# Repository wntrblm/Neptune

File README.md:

# Winterbloom Neptune

Neptune is a *salty* diode ladder filter.

More details available at https://winterbloom.com/shop/neptune

## Repository layout

This repository contains the hardware design files and user guide for Neptune:

- **factory/** contains the scripts used to program, test, and calibrate the module after assembly. These scripts are all written in Python.
- **hardware/** contains the hardware design files for the mainboard and blank panel, as well as hardware for automated testing. These are all created using KiCAD.
- **user_guide/** contains the user's guide source files. These are written in Markdown and published using MkDocs.
- **simulation/** contains the simulation used to design this filter. These should be opened using the Falstad CircuitJS simulator https://www.falstad.com/circuit/circuitjs.html.

## License and contributing

Neptune is open-source hardware and software, however, licensing a project like this is a little complicated. Please take a chance to review the [LICENSE](LICENSE.md) file.

We welcome contributions! Please read our [Code of Conduct](CODE_OF_CONDUCT.md) first.

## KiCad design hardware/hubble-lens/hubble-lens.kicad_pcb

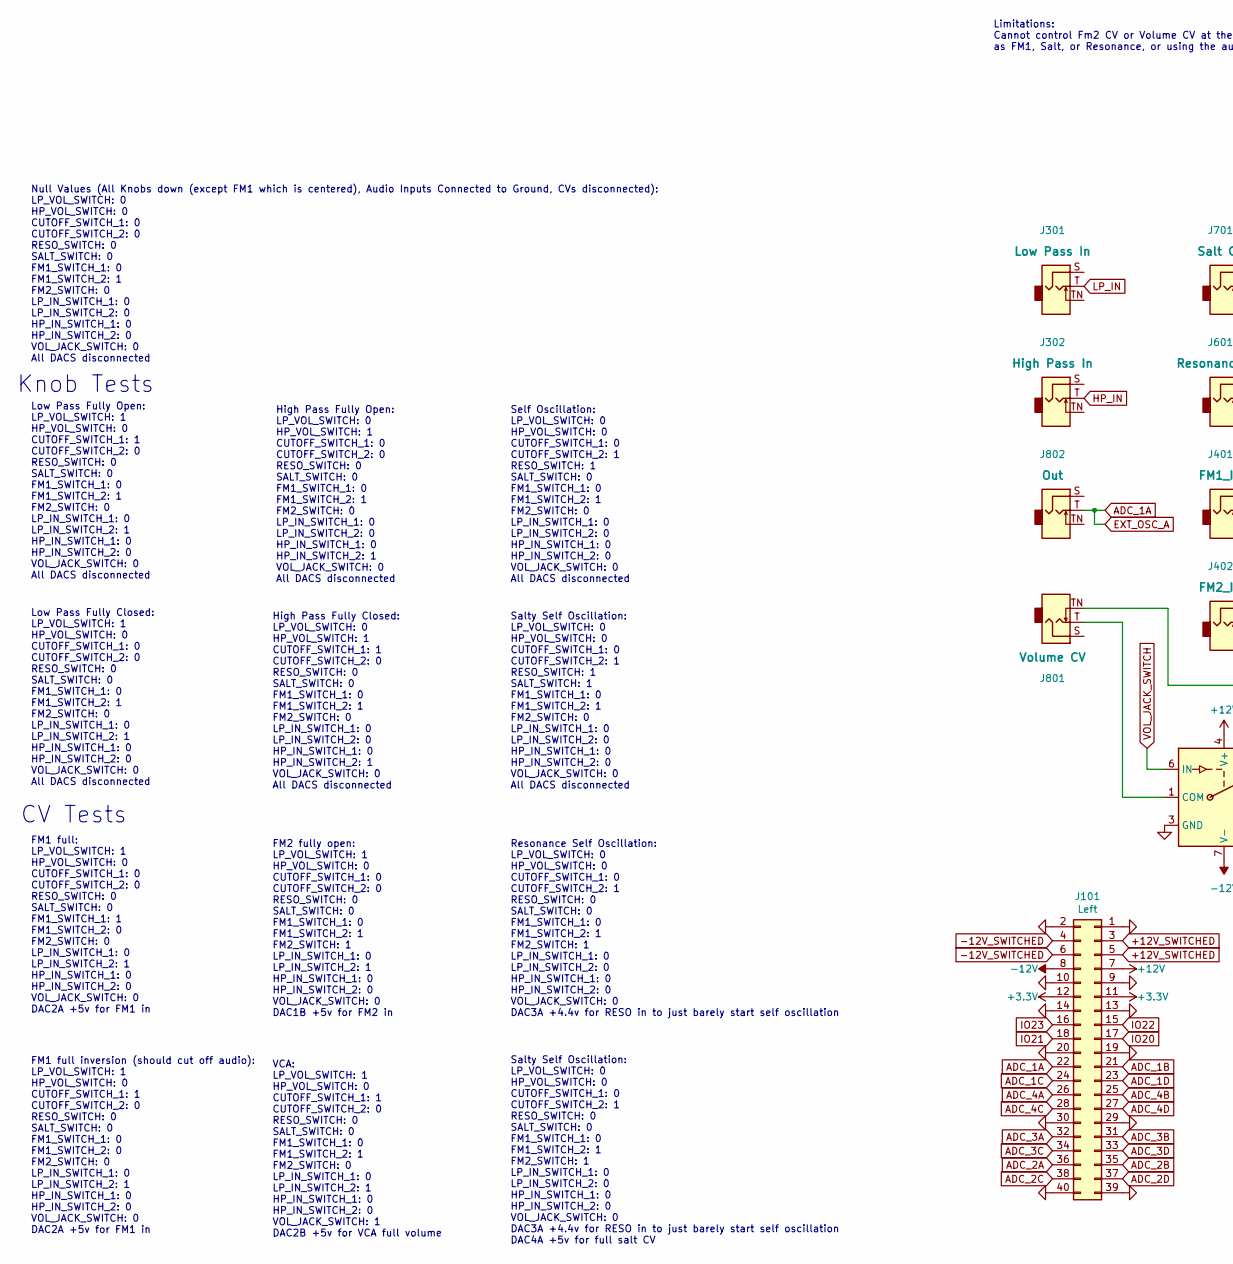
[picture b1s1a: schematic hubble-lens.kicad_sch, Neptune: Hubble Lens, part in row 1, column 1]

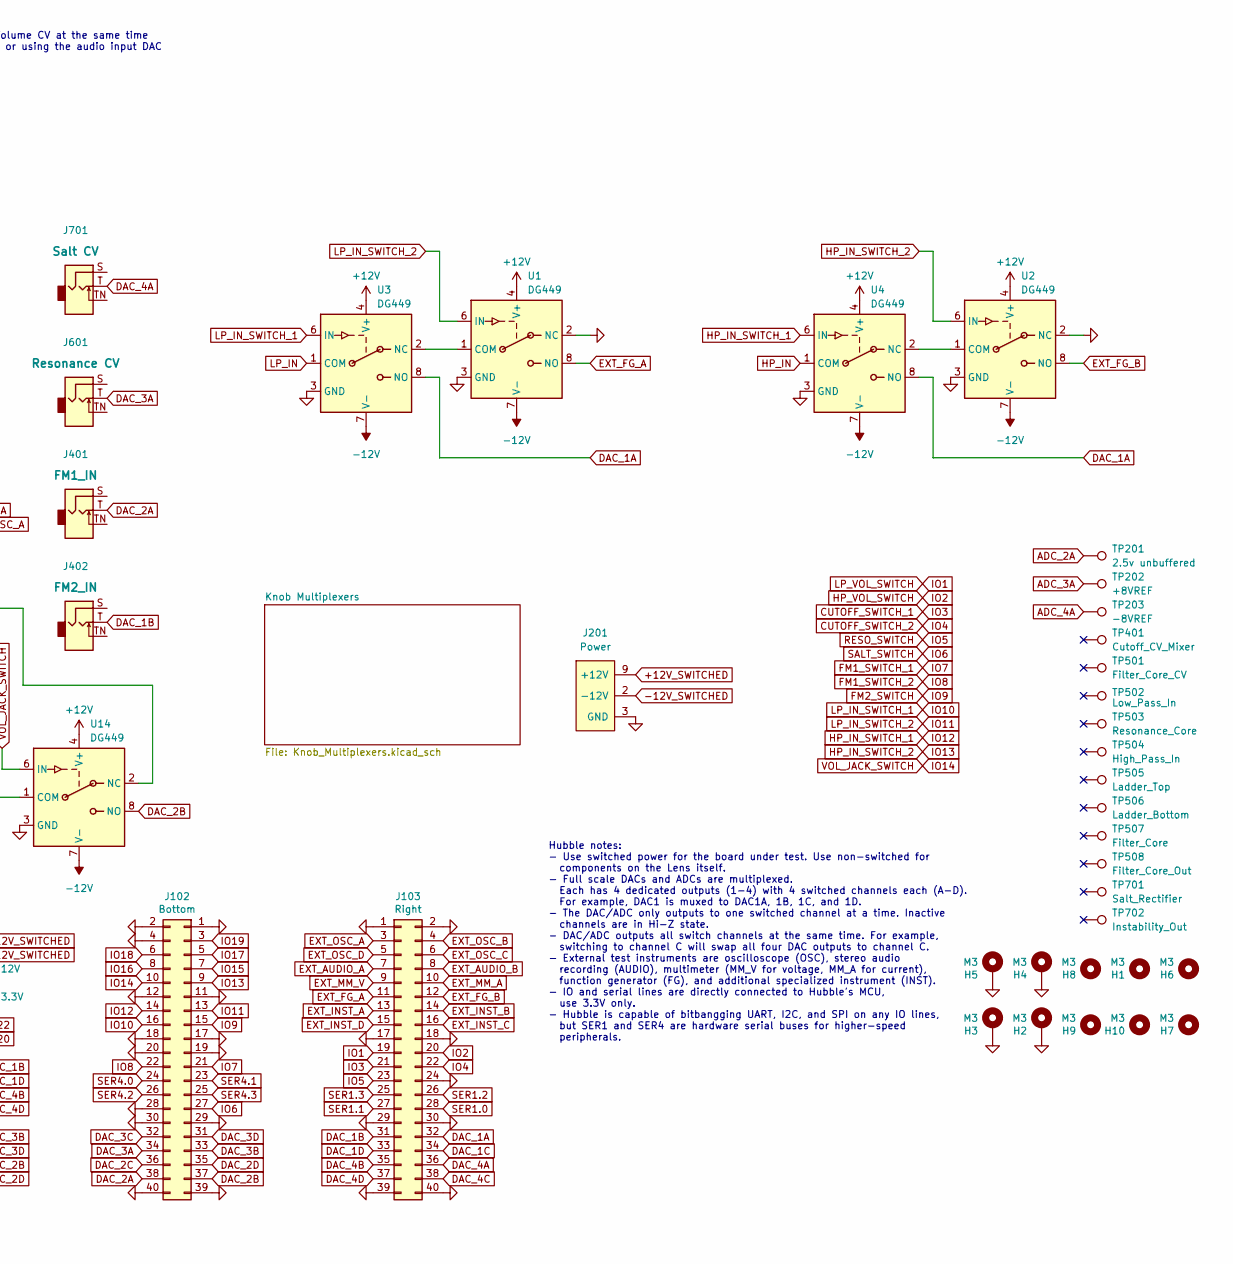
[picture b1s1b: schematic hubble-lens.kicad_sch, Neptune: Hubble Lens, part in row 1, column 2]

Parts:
H1, H6, H7, H8, H9, H10: M3; MountingHole_3.2mm_M3
H2, H3, H4, H5: M3; MountingHole_3.2mm_M3_Pad_Via
J101: Left; PinSocket_2x20_P2.54mm_Vertical
J102: Bottom; PinSocket_2x20_P2.54mm_Vertical
J103: Right; PinSocket_2x20_P2.54mm_Vertical
J201: Power; Eurorack_Power_2x5_Shrouded_Lock; MPN 302-S101
J301, J302, J401, J402, J601, J701, J801, J802: AudioJack_WQP518MA_Compact_S; MPN WQP-WQP518MA
TP201, TP202, TP203, TP401, TP501, TP502, TP503, TP504, TP505, TP506, TP507, TP508, TP701, TP702: TestPoint_THTPad_D2.0mm_Drill1.0mm
U1, U2, U3, U4, U14: DG449; Vishay_SOT-23_8

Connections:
+3V3: J101.11, J101.12
+12V: J101.7, U1.4 (V+), U2.4 (V+), U3.4 (V+), U4.4 (V+), U14.4 (V+); also elsewhere on the board
+12V_SWITCHED: J101.3, J101.5, J201.9 (+12V), J201.10 (+12V)
-12V: J101.8, U1.7 (V-), U2.7 (V-), U3.7 (V-), U4.7 (V-), U14.7 (V-); also elsewhere on the board
-12V_SWITCHED: J101.4, J101.6, J201.1 (-12V), J201.2 (-12V)
ADC_1A: J101.22, J103.3, J802.T (Tip)
ADC_1B: J101.21
ADC_1C: J101.24
ADC_1D: J101.23
ADC_2A: J101.36, TP201.1
ADC_2B: J101.35
ADC_2C: J101.38
ADC_2D: J101.37
ADC_3A: J101.32, TP202.1
ADC_3B: J101.31
ADC_3C: J101.34
ADC_3D: J101.33
ADC_4A: J101.26, TP203.1
ADC_4B: J101.25
ADC_4C: J101.28
ADC_4D: J101.27
CUTOFF_SWITCH_1: J103.21; also elsewhere on the board
CUTOFF_SWITCH_2: J103.22; also elsewhere on the board
DAC_1A: J103.32, U3.8 (NO), U4.8 (NO)
DAC_1B: J103.31, J402.T (Tip)
DAC_1C: J103.34
DAC_1D: J103.33
DAC_2A: J102.38, J401.T (Tip)
DAC_2B: J102.37, U14.8 (NO)
DAC_2C: J102.36
DAC_2D: J102.35
DAC_3A: J102.34, J601.T (Tip)
DAC_3B: J102.33
DAC_3C: J102.32
DAC_3D: J102.31
DAC_4A: J103.36, J701.T (Tip)
DAC_4B: J103.35
DAC_4C: J103.38
DAC_4D: J103.37
EXT_AUDIO_A: J103.7
EXT_AUDIO_B: J103.8
EXT_FG_A: J103.11, U1.8 (NO)
EXT_FG_B: J103.12, U2.8 (NO)
EXT_INST_A: J103.13
EXT_INST_B: J103.14
EXT_INST_C: J103.16
EXT_INST_D: J103.15
EXT_MM_A: J103.10
EXT_MM_V: J103.9
EXT_OSC_B: J103.4
EXT_OSC_C: J103.6
EXT_OSC_D: J103.5
FM1_SWITCH_1: J102.21; also elsewhere on the board
FM1_SWITCH_2: J102.22; also elsewhere on the board
FM2_SWITCH: J102.15; also elsewhere on the board
GND: H2.1, H3.1, H4.1, H5.1, J101.1, J101.2, J101.9, J101.10, J101.13, J101.14, J101.19, J101.20, J101.29, J101.30, J101.39, J101.40, J102.1, J102.2, J102.4, J102.11, J102.12, J102.17, J102.18, J102.19, J102.20, J102.28, J102.29, J102.30, J102.39, J102.40, J103.1, J103.2, J103.17, J103.18, J103.24, J103.29, J103.30, J103.39, J103.40, J201.3 (GND), J201.4 (GND), J201.5 (GND), J201.6 (GND), J201.7 (GND), J201.8 (GND), U1.2 (NC), U1.3 (GND), U2.2 (NC), U2.3 (GND), U3.3 (GND), U4.3 (GND), U14.3 (GND); also elsewhere on the board
HP_IN: J302.T (Tip), U4.1 (COM)
HP_IN_SWITCH_1: J102.14, U4.6 (IN)
HP_IN_SWITCH_2: J102.9, U2.6 (IN)
HP_VOL_SWITCH: J103.20; also elsewhere on the board
IO1: J103.19; also elsewhere on the board
IO5: J103.23; also elsewhere on the board
IO6: J102.27; also elsewhere on the board
IO10: J102.16, U3.6 (IN)
IO11: J102.13, U1.6 (IN)
IO14: J102.10, U14.6 (IN)
IO15: J102.7
IO16: J102.8
IO17: J102.5
IO18: J102.6
IO19: J102.3
IO20: J101.17
IO21: J101.18
IO22: J101.15
IO23: J101.16
LP_IN: J301.T (Tip), U3.1 (COM)
unnamed: J801.T (Tip), U14.1 (COM)
unnamed: J801.TN (Tip_normalize), U14.2 (NC)
unnamed: U1.1 (COM), U3.2 (NC)
unnamed: U2.1 (COM), U4.2 (NC)
SER1.0: J103.28
SER1.1: J103.27
SER1.2: J103.26
SER1.3: J103.25
SER4.0: J102.24
SER4.1: J102.23
SER4.2: J102.26
SER4.3: J102.25

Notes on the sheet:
Null Values (All Knobs down (except FM1 which is centered), Audio Inputs Connected to Ground, CVs disconnected): LP_VOL_SWITCH: 0 HP_VOL_SWITCH: 0 CUTOFF_SWITCH_1: 0 CUTOFF_SWITCH_2: 0 RESO_SWITCH: 0 SALT_SWITCH: 0 FM1_SWITCH_1: 0 FM1_SWITCH_2: 1 FM2_SWITCH: 0 LP_IN_SWITCH_1: 0 LP_IN_SWITCH_2: 0 HP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
Self Oscillation: LP_VOL_SWITCH: 0 HP_VOL_SWITCH: 0 CUTOFF_SWITCH_1: 0 CUTOFF_SWITCH_2: 1 RESO_SWITCH: 1 SALT_SWITCH: 0 FM1_SWITCH_1: 0 FM1_SWITCH_2: 1 FM2_SWITCH: 0 LP_IN_SWITCH_1: 0 LP_IN_SWITCH_2: 0 HP_IN_SWITCH_1: 0 HP_IN_SWITCH_2: 0 VOL_JACK_SWITCH: 0 All DACS disconnected
Knob Tests
Limitations: Cannot control Fm2 CV or Volume CV at the same time as FM1, Salt, or Resonance, or using the audio input DAC
VCA: LP_VOL_SWITCH: 1 HP_VOL_SWITCH: 0 CUTOFF_SWITCH_1: 1 CUTOFF_SWITCH_2: 0 RESO_SWITCH: 0 SALT_SWITCH: 0 FM1_SWITCH_1: 0 FM1_SWITCH_2: 1 FM2_SWITCH: 0 LP_IN_SWITCH_1: 0 LP_IN_SWITCH_2: 1 HP_IN_SWITCH_1: 0 HP_IN_SWITCH_2: 0 VOL_JACK_SWITCH: 1 DAC2B +5v for VCA full volume
CV Tests
Salty Self Oscillation: LP_VOL_SWITCH: 0 HP_VOL_SWITCH: 0 CUTOFF_SWITCH_1: 0 CUTOFF_SWITCH_2: 1 RESO_SWITCH: 0 SALT_SWITCH: 0 FM1_SWITCH_1: 0 FM1_SWITCH_2: 1 FM2_SWITCH: 1 LP_IN_SWITCH_1: 0 LP_IN_SWITCH_2: 0 HP_IN_SWITCH_1: 0 HP_IN_SWITCH_2: 0 VOL_JACK_SWITCH: 0 DAC3A +4.4v for RESO in to just bare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
High Pass Fully Closed: LP_VOL_SWITCH: 0 HP_VOL_SWITCH: 1 CUTOFF_SWITCH_1: 1 CUTOFF_SWITCH_2: 0 RESO_SWITCH: 0 SALT_SWITCH: 0 FM1_SWITCH_1: 0 FM1_SWITCH_2: 1 FM2_SWITCH: 0 LP_IN_SWITCH_1: 0 LP_IN_SWITCH_2: 0 HP_IN_SWITCH_1: 0 HP_IN_SWITCH_2: 1 VOL_JACK_SWITCH: 0 All DACS disconnected
FM1 full inversion (should cut off audio): LP_VOL_SWITCH: 1 HP_VOL_SWITCH: 0 CUTOFF_SWITCH_1: 1 CUTOFF_SWITCH_2: 0 RESO_SWITCH: 0 SALT_SWITCH: 0 FM1_SWITCH_1: 0 FM1_SWITCH_2: 0 FM2_SWITCH: 0 LP_IN_SWITCH_1: 0 LP_IN_SWITCH_2: 1 HP_IN_SWITCH_1: 0 HP_IN_SWITCH_2: 0 VOL_JACK_SWITCH: 0 DAC2A +5v for FM1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
Hubble notes: - Use switched power for the board under test. Use non-switched for components on the Lens itself. - Full scale DACs and ADCs are multiplexed. Each has 4 dedicated outputs (1-4) with 4 switched channels each (A-D). For example, DAC1 is muxed to DAC1A, 1B, 1C, and 1D. - The DAC/ADC onl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
FM2 fully open: LP_VOL_SWITCH: 1 HP_VOL_SWITCH: 0 CUTOFF_SWITCH_1: 0 CUTOFF_SWITCH_2: 0 RESO_SWITCH: 0 SALT_SWITCH: 0 FM1_SWITCH_1: 0 FM1_SWITCH_2: 1 FM2_SWITCH: 1 LP_IN_SWITCH_1: 0 LP_IN_SWITCH_2: 1 HP_IN_SWITCH_1: 0 HP_IN_SWITCH_2: 0 VOL_JACK_SWITCH: 0 DAC1B +5v for FM2 in
Low Pass Fully Closed: LP_VOL_SWITCH: 1 HP_VOL_SWITCH: 0 CUTOFF_SWITCH_1: 0 CUTOFF_SWITCH_2: 0 RESO_SWITCH: 0 SALT_SWITCH: 0 FM1_SWITCH_1: 0 FM1_SWITCH_2: 1 FM2_SWITCH: 0 LP_IN_SWITCH_1: 0 LP_IN_SWITCH_2: 1 HP_IN_SWITCH_1: 0 HP_IN_SWITCH_2: 0 VOL_JACK_SWITCH: 0 All DACS disconnected
FM1 full: LP_VOL_SWITCH: 1 HP_VOL_SWITCH: 0 CUTOFF_SWITCH_1: 0 CUTOFF_SWITCH_2: 0 RESO_SWITCH: 0 SALT_SWITCH: 0 FM1_SWITCH_1: 1 FM1_SWITCH_2: 0 FM2_SWITCH: 0 LP_IN_SWITCH_1: 0 LP_IN_SWITCH_2: 1 HP_IN_SWITCH_1: 0 HP_IN_SWITCH_2: 0 VOL_JACK_SWITCH: 0 DAC2A +5v for FM1 in
Low Pass Fully Open: LP_VOL_SWITCH: 1 HP_VOL_SWITCH: 0 CUTOFF_SWITCH_1: 1 CUTOFF_SWITCH_2: 0 RESO_SWITCH: 0 SALT_SWITCH: 0 FM1_SWITCH_1: 0 FM1_SWITCH_2: 1 FM2_SWITCH: 0 LP_IN_SWITCH_1: 0 LP_IN_SWITCH_2: 1 HP_IN_SWITCH_1: 0 HP_IN_SWITCH_2: 0 VOL_JACK_SWITCH: 0 All DACS disconnected
Salty Self Oscillation: LP_VOL_SWITCH: 0 HP_VOL_SWITCH: 0 CUTOFF_SWITCH_1: 0 CUTOFF_SWITCH_2: 1 RESO_SWITCH: 1 SALT_SWITCH: 1 FM1_SWITCH_1: 0 FM1_SWITCH_2: 1 FM2_SWITCH: 0 LP_IN_SWITCH_1: 0 LP_IN_SWITCH_2: 0 HP_IN_SWITCH_1: 0 HP_IN_SWITCH_2: 0 VOL_JACK_SWITCH: 0 All DACS disconnected
High Pass Fully Open: LP_VOL_SWITCH: 0 HP_VOL_SWITCH: 1 CUTOFF_SWITCH_1: 0 CUTOFF_SWITCH_2: 0 RESO_SWITCH: 0 SALT_SWITCH: 0 FM1_SWITCH_1: 0 FM1_SWITCH_2: 1 FM2_SWITCH: 0 LP_IN_SWITCH_1: 0 LP_IN_SWITCH_2: 0 HP_IN_SWITCH_1: 0 HP_IN_SWITCH_2: 1 VOL_JACK_SWITCH: 0 All DACS disconnected
Resonance Self Oscillation: LP_VOL_SWITCH: 0 HP_VOL_SWITCH: 0 CUTOFF_SWITCH_1: 0 CUTOFF_SWITCH_2: 1 RESO_SWITCH: 0 SALT_SWITCH: 0 FM1_SWITCH_1: 0 FM1_SWITCH_2: 1 FM2_SWITCH: 1 LP_IN_SWITCH_1: 0 LP_IN_SWITCH_2: 0 HP_IN_SWITCH_1: 0 HP_IN_SWITCH_2: 0 VOL_JACK_SWITCH: 0 DAC3A +4.4v for RESO in to just 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

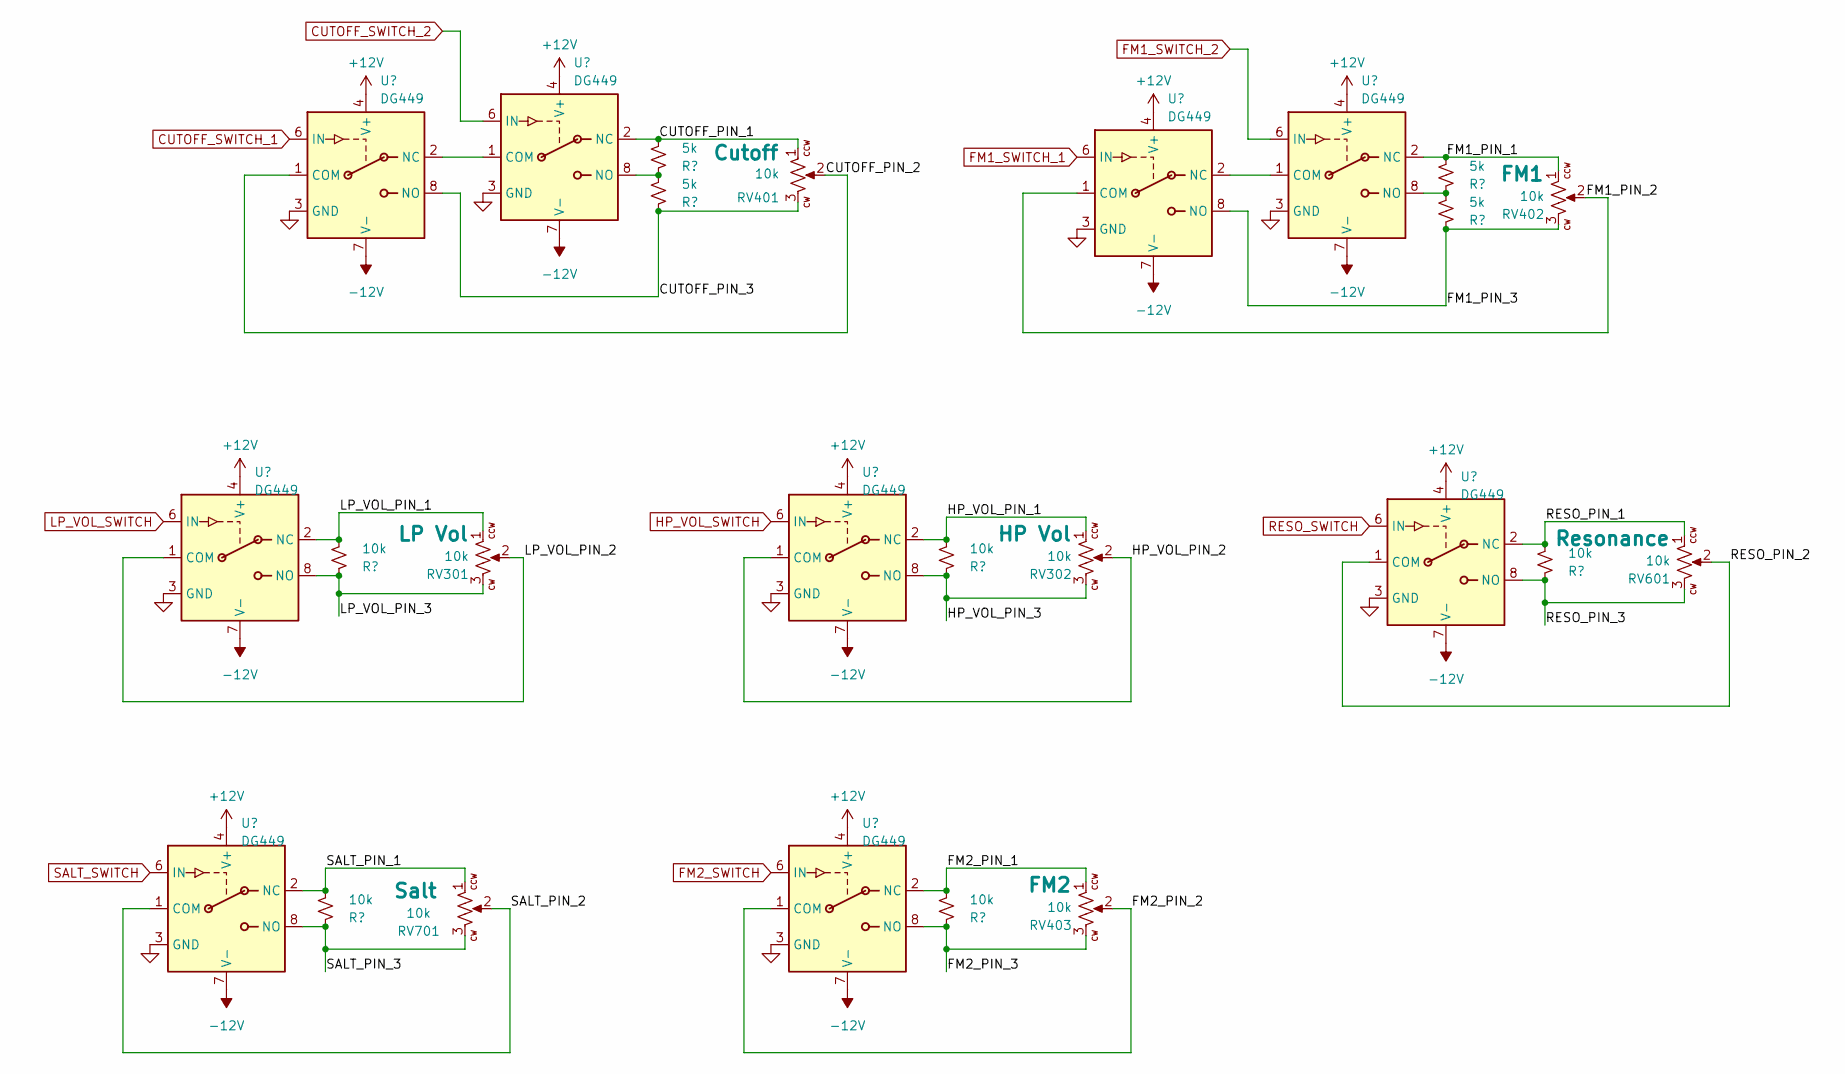
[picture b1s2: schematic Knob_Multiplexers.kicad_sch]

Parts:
R1, R2, R3, R4: 5k; R_0603_HandSolder
R5, R6, R7, R8, R9: 10k; R_0603_HandSolder
RV301, RV302, RV401, RV402, RV403, RV601, RV701: 10k; Potentiometer_Alpha_R0904N; Rating B10k
U5, U6, U7, U8, U9, U10, U11, U12, U13: DG449; Vishay_SOT-23_8

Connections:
+12V: U5.4 (V+), U6.4 (V+), U7.4 (V+), U8.4 (V+), U9.4 (V+), U10.4 (V+), U11.4 (V+), U12.4 (V+), U13.4 (V+); also elsewhere on the board
-12V: U5.7 (V-), U6.7 (V-), U7.7 (V-), U8.7 (V-), U9.7 (V-), U10.7 (V-), U11.7 (V-), U12.7 (V-), U13.7 (V-); also elsewhere on the board
/Knob Multiplexers/CUTOFF_PIN_1: R1.2, RV401.1, U5.2 (NC)
/Knob Multiplexers/CUTOFF_PIN_2: RV401.2, U6.1 (COM)
/Knob Multiplexers/CUTOFF_PIN_3: R3.1, RV401.3, U6.8 (NO)
/Knob Multiplexers/FM1_PIN_1: R2.2, RV402.1, U7.2 (NC)
/Knob Multiplexers/FM1_PIN_2: RV402.2, U8.1 (COM)
/Knob Multiplexers/FM1_PIN_3: R4.1, RV402.3, U8.8 (NO)
/Knob Multiplexers/FM2_PIN_1: R9.2, RV403.1, U13.2 (NC)
/Knob Multiplexers/FM2_PIN_2: RV403.2, U13.1 (COM)
/Knob Multiplexers/FM2_PIN_3: R9.1, RV403.3, U13.8 (NO)
/Knob Multiplexers/HP_VOL_PIN_1: R6.2, RV302.1, U10.2 (NC)
/Knob Multiplexers/HP_VOL_PIN_2: RV302.2, U10.1 (COM)
/Knob Multiplexers/HP_VOL_PIN_3: R6.1, RV302.3, U10.8 (NO)
/Knob Multiplexers/LP_VOL_PIN_1: R5.2, RV301.1, U9.2 (NC)
/Knob Multiplexers/LP_VOL_PIN_2: RV301.2, U9.1 (COM)
/Knob Multiplexers/LP_VOL_PIN_3: R5.1, RV301.3, U9.8 (NO)
/Knob Multiplexers/RESO_PIN_1: R7.2, RV601.1, U11.2 (NC)
/Knob Multiplexers/RESO_PIN_2: RV601.2, U11.1 (COM)
/Knob Multiplexers/RESO_PIN_3: R7.1, RV601.3, U11.8 (NO)
/Knob Multiplexers/SALT_PIN_1: R8.2, RV701.1, U12.2 (NC)
/Knob Multiplexers/SALT_PIN_2: RV701.2, U12.1 (COM)
/Knob Multiplexers/SALT_PIN_3: R8.1, RV701.3, U12.8 (NO)
CUTOFF_SWITCH_1: U6.6 (IN); also elsewhere on the board
CUTOFF_SWITCH_2: U5.6 (IN); also elsewhere on the board
FM1_SWITCH_1: U8.6 (IN); also elsewhere on the board
FM1_SWITCH_2: U7.6 (IN); also elsewhere on the board
FM2_SWITCH: U13.6 (IN); also elsewhere on the board
GND: U5.3 (GND), U6.3 (GND), U7.3 (GND), U8.3 (GND), U9.3 (GND), U10.3 (GND), U11.3 (GND), U12.3 (GND), U13.3 (GND); also elsewhere on the board
HP_VOL_SWITCH: U10.6 (IN); also elsewhere on the board
IO1: U9.6 (IN); also elsewhere on the board
IO5: U11.6 (IN); also elsewhere on the board
IO6: U12.6 (IN); also elsewhere on the board
unnamed: U5.1 (COM), U6.2 (NC)
unnamed: R1.1, R3.2, U5.8 (NO)
unnamed: U7.1 (COM), U8.2 (NC)
unnamed: R2.1, R4.2, U7.8 (NO)

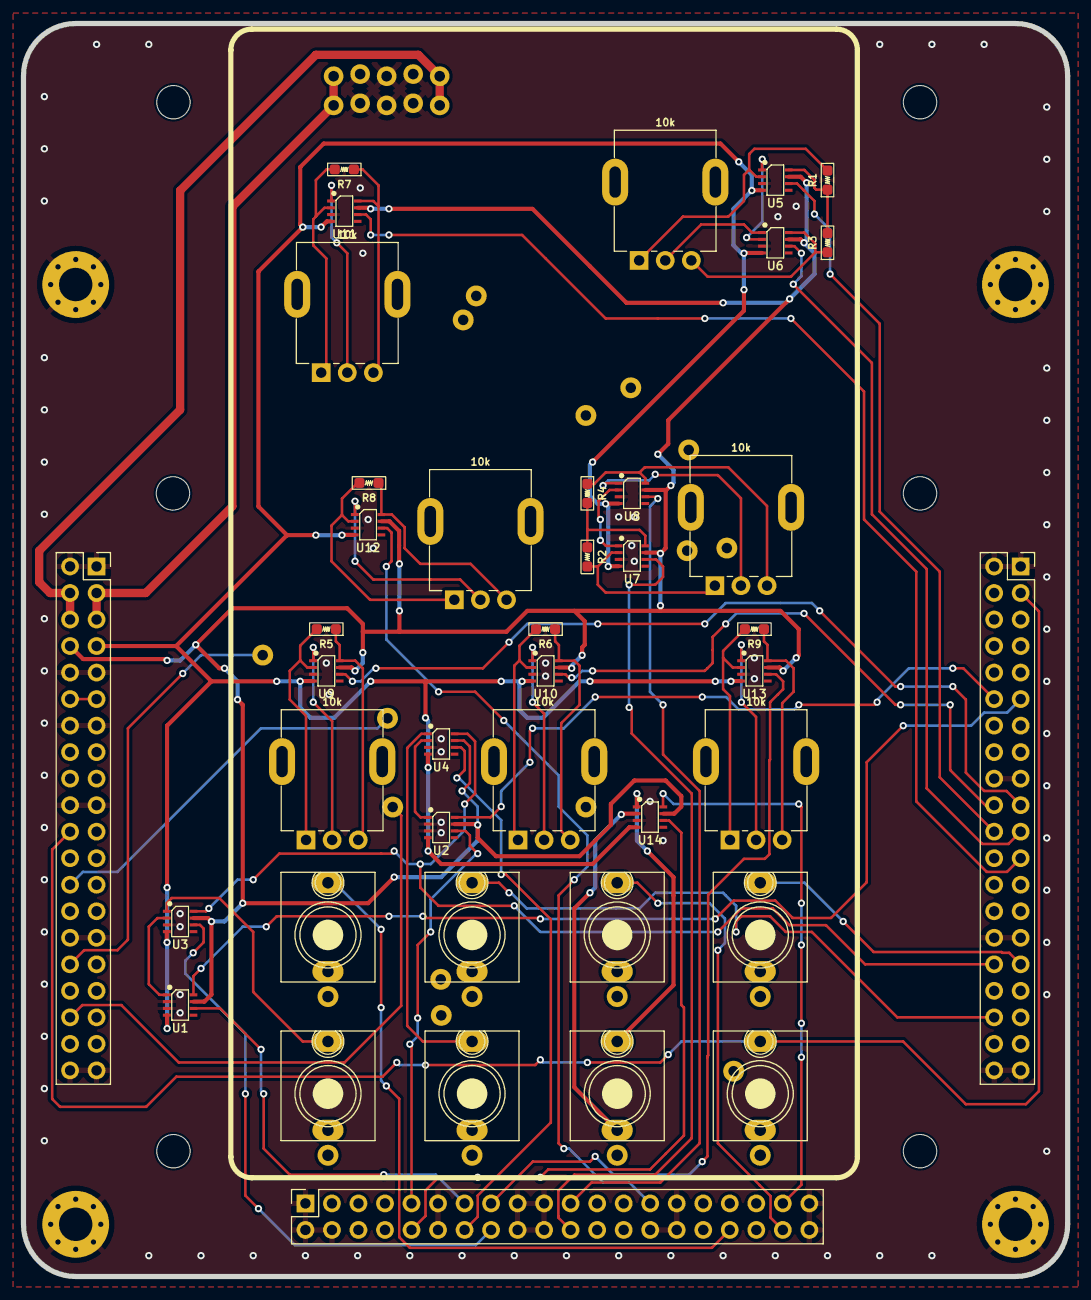
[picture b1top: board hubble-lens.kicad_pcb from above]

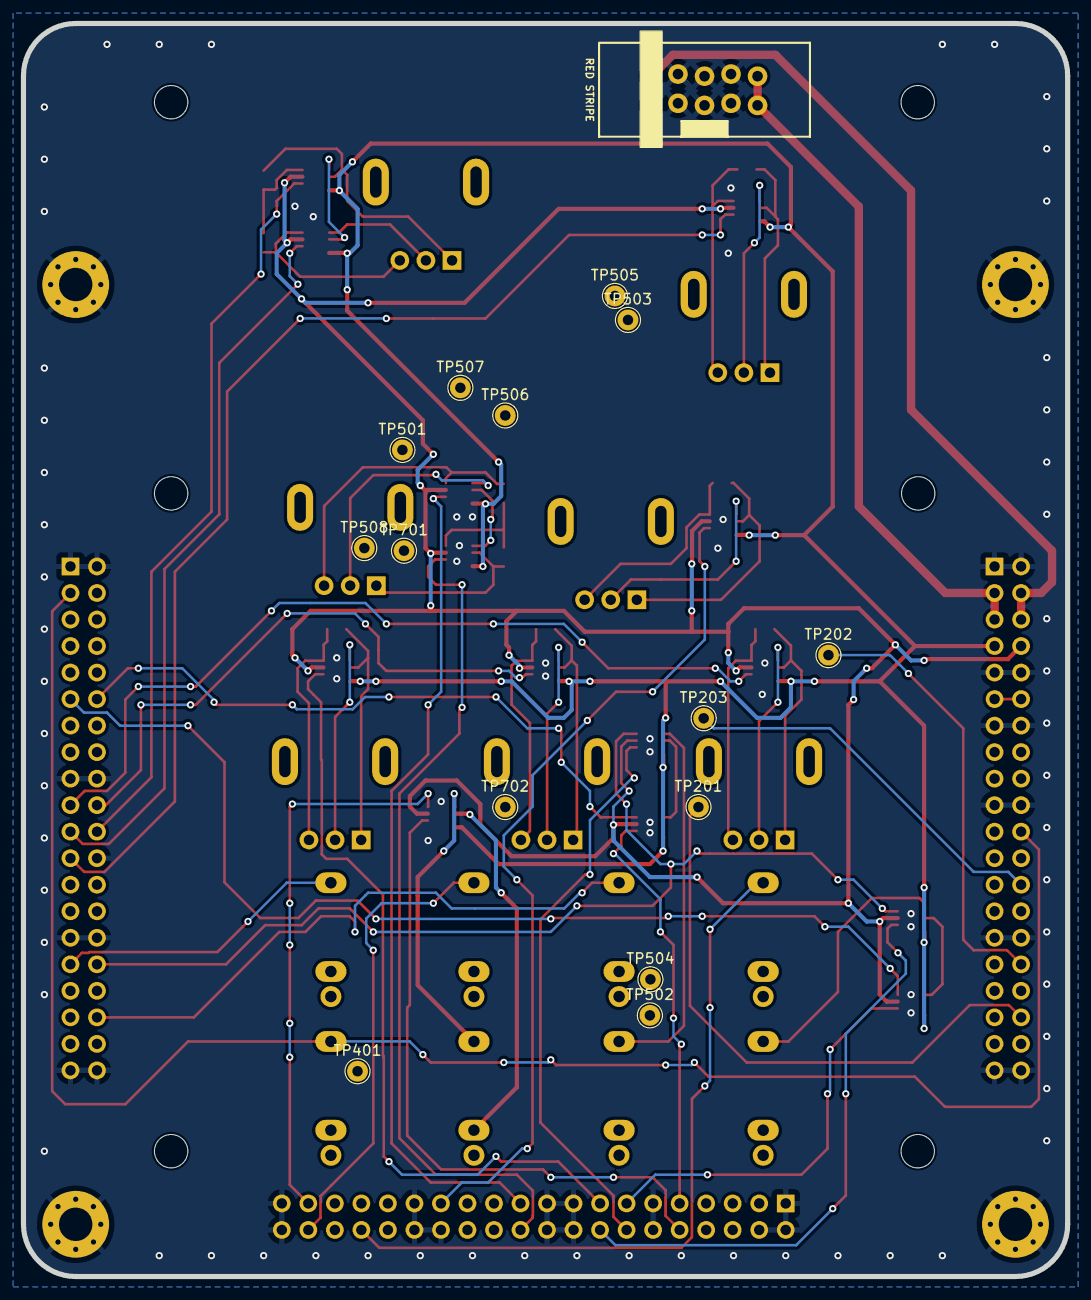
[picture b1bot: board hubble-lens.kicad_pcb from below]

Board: 2 copper layers, 100.0 x 120.0 mm, 66 parts (15 on the bottom side), 63 nets.

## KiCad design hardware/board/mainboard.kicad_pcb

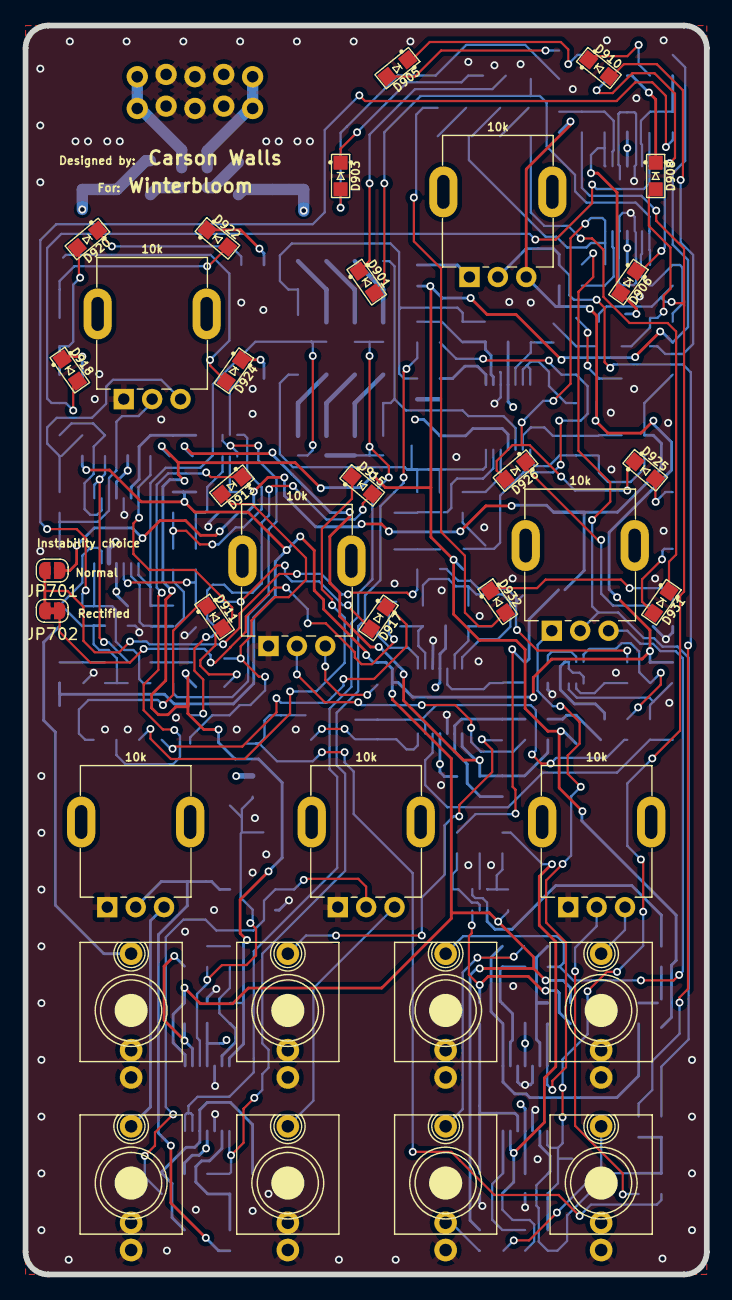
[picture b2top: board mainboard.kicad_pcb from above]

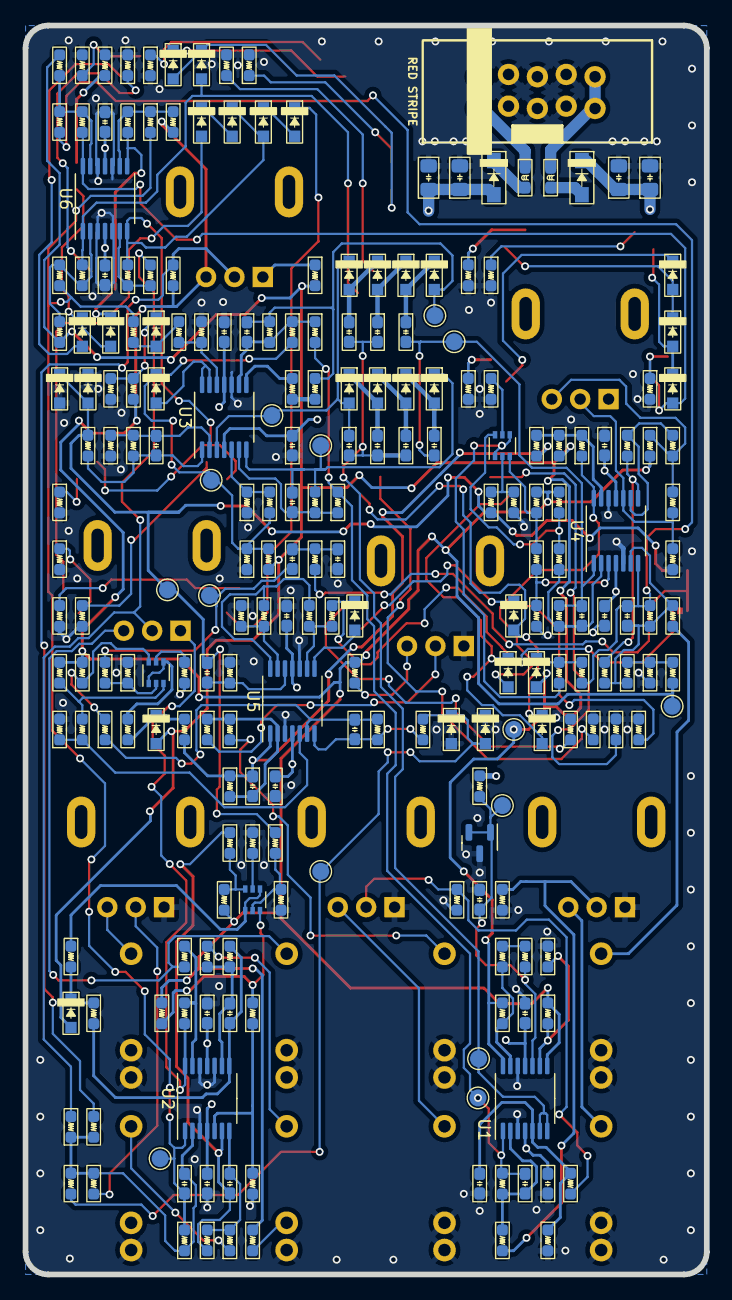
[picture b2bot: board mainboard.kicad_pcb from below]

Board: 4 copper layers, 60.0 x 110.0 mm, 266 parts (231 on the bottom side), 150 nets.

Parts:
C201, C202, C203, C204: 10u; C_0805_HandSolder
C205, C206, C207, C208, C209, C210, C211, C212, C213, C214, C215, C216, C217: 100n; C_0603_HandSolder
C301, C302, C503, C504, C505, C506, C507, C508, C509: 1n; C_0603_HandSolder
C401, C510: 100p; C_0603_HandSolder
C501, C502, C702: 220p; C_0603_HandSolder
C601, C704, C801: 330p; C_0603_HandSolder
C602, C705: 68p; C_0603_HandSolder
C701, C703: 220n; C_0603_HandSolder
C802: 10p; C_0603_HandSolder
D201, D202: 30V; D_SOD-123+SOD-123F
D501, D502, D503, D504, D505, D506, D507, D508, D509, D510, D511, D512, D601, D701, D702, D703, D704, D801, D902, D904, D907, D909, D912, D914, D916, D919, D921, D923, D927, D928, D929, D930: BAS315; D_SOD-323
D901, D903, D905, D906, D908, D910, D918, D920, D922, D925, D931: BLUE; LED_0805_Kingbright_APT2012
D911, D913, D915, D917, D924, D926, D932: RED; LED_0805_Kingbright_APT2012
FB201, FB202: 1k @ 100MHz; L_0603_HandSolder
J201: Power; Eurorack_Power_2x5_Shrouded_Lock
J301, J302, J401, J402, J601, J701, J801, J802: AudioJack_WQP518MA_Compact_S
JP701: SolderJumper_2_Open; SolderJumper-2_P1.3mm_Open_RoundedPad1.0x1.5mm
JP702: SolderJumper_2_Bridged; SolderJumper-2_P1.3mm_Bridged_RoundedPad1.0x1.5mm
Q601, Q701, Q801: BCM847; SOT-363_SC-70-6
R201, R203, R303, R306, R502, R515, R516, R519, R603, R604, R605, R612, R704, R705, R713, R722, R804, R815, R906, R912, R919, R926, R931, R932: 1k; R_0603_HandSolder
R202, R302, R305, R403, R404, R505, R606, R607, R609, R610, R611, R702, R710, R711, R712, R914, R927, R928: 100k; R_0603_HandSolder
R204, R405, R409, R518, R802, R803: 68k; R_0603_HandSolder
R205, R206, R720, R721: 220k; R_0603_HandSolder
R301, R304, R501, R504, R602, R709, R903, R909: 5k6; R_0603_HandSolder
R401, R517, R614, R619, R620, R718, R719: 3k9; R_0603_HandSolder
R402, R706, R707, R801: 39k; R_0603_HandSolder
R406, R407, R507, R621, R622, R902, R922: 33k; R_0603_HandSolder
R408, R601, R613, R701, R703, R714, R805, R806, R811, R812, R901, R907, R908, R913, R915, R920: 10k; R_0603_HandSolder
R503, R608, R813, R814, R921: 330k; R_0603_HandSolder
R506, R508, R509, R510, R511, R512, R513, R514, R617, R618, R716, R717, R809, R810: 20k; R_0603_HandSolder
R615, R616, R708, R715, R807, R808: 100R; R_0603_HandSolder
R904, R910, R917, R924, R929, R930: 1k5; R_0603_HandSolder
R905, R911, R918, R925: 1.2k; R_0603_HandSolder
R916, R923: 1.8k; R_0603_HandSolder
RV301, RV302, RV401, RV402, RV403, RV601, RV701: 10k; Potentiometer_Alpha_R0904N
TP201, TP202, TP203, TP401, TP501, TP502, TP503, TP504, TP505, TP506, TP507, TP508, TP701, TP702: TestPoint_Pad_D1.5mm
U1, U2, U3, U4, U5, U6: TL074; TSSOP-14_4.4x5mm_P0.65mm
U201: TL431A; SOT-23

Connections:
+8VREF: R205.1, R402.1, R504.1, R601.1, R602.2, R617.2, R618.1, R709.2, R716.2, R717.1, R801.2, R809.2, R810.1, R908.2, RV401.3, TP202.1, U1.8
+12V: C201.1, C203.1, C206.2, C208.2, C210.2, C212.2, C214.2, C216.2, D201.1 (K), R201.1, U1.4 (V+), U2.4 (V+), U3.4 (V+), U4.4 (V+), U5.4 (V+), U6.4 (V+)
-8VREF: D601.2 (A), D702.2 (A), D801.2 (A), R206.1, R401.2, R506.2, R902.2, R914.2, R921.2, TP203.1, U1.14
-12V: C202.1, C204.1, C207.2, C209.2, C211.2, C213.2, C215.2, C217.2, D202.2 (A), U1.11 (V-), U2.11 (V-), U3.11 (V-), U4.11 (V-), U5.11 (V-), U6.11 (V-)
/Cutoff CV Driver/CUTOFF_OUT: C401.1, R409.2, R501.2, R901.2, R907.2, TP401.1, U2.1
/Cutoff CV Driver/FM1_OUT: R406.2, R927.2, RV402.2
/Cutoff CV Driver/INSTABILITY_IN: D703.1 (K), D704.2 (A), R408.2, R722.1, TP702.1
/Filter Core/HIGH_PASS_IN: C504.2, C505.2, C506.2, C507.2, C508.2, TP504.1, U1.6 (-), U1.7
/Filter Core/LOW_PASS_IN: C301.1, R303.1, R509.2, R510.2, TP502.1, U1.1
/Filter Core/OUT: C701.2, D511.1 (K), D512.2 (A), JP701.1 (A), R519.2, R614.2, R805.1, TP508.1
/Filter Core/RESONANCE_IN: C503.2, C509.2, C602.1, R622.1, TP503.1, U4.1
/Instability VCA/INSTABILITY_CV_OUT: C704.1, R712.1, R713.2, R913.2, U5.1
/LED Drivers/RESONANCE_CV_IN: C601.1, R611.1, R612.2, R920.2, U4.7
/Power/2.5v unbuffered: C205.2, R201.2, R203.1, TP201.1, U1.10 (+), U201.1 (K), U201.2 (REF)
/Resonance VCA/Resonance_CV: J601.T (Tip), R608.2
/Resonance VCA/Resonance_Offset: R601.2, R603.2, R609.2
/Resonance VCA/Resonance_Potentiometer: R607.1, R610.2, U4.8
GND: C201.2, C202.2, C203.2, C204.2, C205.1, C206.1, C207.1, C208.1, C209.1, C210.1, C211.1, C212.1, C213.1, C214.1, C215.1, C216.1, C217.1, C302.2, C702.2, D511.2 (A), D512.1 (K), D703.2 (A), D704.1 (K), J201.3 (GND), J201.4 (GND), J201.5 (GND), J201.6 (GND), J201.7 (GND), J201.8 (GND), J301.S (Sleeve), J301.TN (Tip_normalize), J302.S (Sleeve), J302.TN (Tip_normalize), J401.S (Sleeve), J401.TN (Tip_normalize), J402.S (Sleeve), J402.TN (Tip_normalize), J601.S (Sleeve), J601.TN (Tip_normalize), J701.S (Sleeve), J701.TN (Tip_normalize), J801.S (Sleeve), J802.S (Sleeve), R202.2, R301.2, R304.2, R306.2, R502.2, R505.2, R507.1, R512.1, R517.1, R603.1, R605.2, R615.2, R616.1, R621.2, R701.2, R702.1, R708.2, R715.1, R720.2, R807.2, R808.1, R813.2, R904.2, R905.2, R906.2, R910.2, R911.2, R912.2, R916.2, R917.2, R918.2, R919.2, R923.2, R924.2, R925.2, R926.2, R929.2, R930.2, R931.2, R932.2, RV301.1, RV302.1, RV403.1, RV601.1, RV701.1, U1.3 (+), U1.12 (+), U2.3 (+), U2.10 (+), U2.12 (+), U3.10 (+), U4.5 (+), U4.12 (+), U5.3 (+), U5.10 (+), U6.3 (+), U6.5 (+), U6.10 (+), U6.12 (+), U201.3 (A)
unnamed: C510.1, R518.2, R519.1, U3.1
unnamed: C702.1, C703.2, R706.1
unnamed: C703.1, R707.1, TP701.1
unnamed: C705.1, R721.1, R722.2, U5.7
unnamed: C801.1, R803.1, R804.2, U2.8
unnamed: C802.2, R814.1, R815.2, U2.7
unnamed: D201.2 (A), FB201.1
unnamed: D202.1 (K), FB202.1
unnamed: D501.2 (A), R501.1, R503.2
unnamed: D501.1 (K), R502.1, R504.2
unnamed: D502.2 (A), U3.13 (-), U3.14
unnamed: D502.1 (K), R506.1, R507.2, R508.2, R511.2, TP501.1
unnamed: C501.1, D503.2 (A), R513.1, R515.1, TP505.1
unnamed: C503.1, D503.1 (K), D504.2 (A)
unnamed: C504.1, D504.1 (K), D505.2 (A)
unnamed: C505.1, D505.1 (K), D506.2 (A)
unnamed: C506.1, D506.1 (K), D507.2 (A), TP507.1, U3.3 (+)
unnamed: C507.1, D507.1 (K), D508.2 (A)
unnamed: C508.1, D508.1 (K), D509.2 (A)
unnamed: C509.1, D509.1 (K), D510.2 (A)
unnamed: C502.1, D510.1 (K), R514.1, TP506.1, U3.7
unnamed: D601.1 (K), R612.1, R613.2
unnamed: D701.2 (A), U5.8
unnamed: D701.1 (K), JP702.2 (B), R705.1
unnamed: D702.1 (K), R713.1, R714.2
unnamed: D801.1 (K), R804.1, R806.2
unnamed: D901.2 (A), D902.2 (A), R903.1, U6.1
unnamed: D901.1 (K), R904.1
unnamed: D902.1 (K), D903.2 (A), D904.2 (A)
unnamed: D903.1 (K), R905.1
unnamed: D904.1 (K), D905.2 (A)
unnamed: D905.1 (K), R906.1
unnamed: D906.2 (A), D907.1 (K), R909.1, U6.8
unnamed: D906.1 (K), R910.1
unnamed: D907.2 (A), D908.2 (A), D909.1 (K)
unnamed: D908.1 (K), R911.1
unnamed: D909.2 (A), D910.2 (A)
unnamed: D910.1 (K), R912.1
unnamed: D911.2 (A), D912.2 (A), R915.1, U4.14
unnamed: D911.1 (K), R916.1
unnamed: D912.1 (K), D913.2 (A), D914.2 (A)
unnamed: D913.1 (K), R917.1
unnamed: D914.1 (K), D915.2 (A), D916.2 (A)
unnamed: D915.1 (K), R918.1
unnamed: D916.1 (K), D917.2 (A)
unnamed: D917.1 (K), R919.1
unnamed: D918.2 (A), D919.2 (A), R922.1, U6.14
unnamed: D918.1 (K), R923.1
unnamed: D919.1 (K), D920.2 (A), D921.2 (A)
unnamed: D920.1 (K), R924.1
unnamed: D921.1 (K), D922.2 (A), D923.2 (A)
unnamed: D922.1 (K), R925.1
unnamed: D923.1 (K), D924.2 (A)
unnamed: D924.1 (K), R926.1
unnamed: D925.2 (A), R929.1
unnamed: D925.1 (K), D926.2 (A), D927.1 (K), D928.2 (A), R928.1, U6.7
unnamed: D926.1 (K), R930.1
unnamed: D927.2 (A), D929.1 (K)
unnamed: D928.1 (K), D930.2 (A)
unnamed: D929.2 (A), D931.1 (K)
unnamed: D930.1 (K), D932.2 (A)
unnamed: D931.2 (A), R931.1
unnamed: D932.1 (K), R932.1
unnamed: FB201.2, J201.9 (+12V), J201.10 (+12V)
unnamed: FB202.2, J201.1 (-12V), J201.2 (-12V)
unnamed: J301.T (Tip), RV301.3
unnamed: J302.T (Tip), RV302.3
unnamed: J401.T (Tip), R403.2, RV402.3
unnamed: J402.T (Tip), RV403.3
unnamed: J701.T (Tip), R710.2
unnamed: J801.T (Tip), R802.2
unnamed: J801.TN (Tip_normalize), R801.1
unnamed: J802.T (Tip), R815.1
unnamed: JP701.2 (B), JP702.1 (A), R706.2
unnamed: Q601.2 (B), R614.1, R615.1
unnamed: Q601.5 (B), R616.2
unnamed: Q601.3 (C), R618.2, R620.2
unnamed: Q601.6 (C), R617.1, R619.2
unnamed: Q601.1 (E), Q601.4 (E), R613.1
unnamed: Q701.2 (B), R707.2, R708.1
unnamed: Q701.5 (B), R715.2
unnamed: Q701.3 (C), R717.2, R719.2
unnamed: Q701.6 (C), R716.1, R718.2
unnamed: Q701.1 (E), Q701.4 (E), R714.1
unnamed: Q801.2 (B), R805.2, R807.1
unnamed: Q801.5 (B), R808.2
unnamed: Q801.3 (C), R810.2, R812.2
unnamed: Q801.6 (C), R809.1, R811.2
unnamed: Q801.1 (E), Q801.4 (E), R806.1
unnamed: R203.2, R204.1
unnamed: R301.1, R302.2, RV301.2
unnamed: R304.1, R305.2, RV302.2
unnamed: R401.1, RV401.1
unnamed: R402.2, R405.1, RV401.2
unnamed: R404.1, RV402.1, U2.14
unnamed: R407.2, RV403.2
unnamed: R515.2, R516.1
unnamed: R516.2, U3.8
unnamed: R602.1, R604.1, R606.2, RV601.3
unnamed: R703.1, R704.2, U5.14
unnamed: R709.1, RV701.3
unnamed: R711.2, RV701.2
unnamed: C301.2, R302.1, R303.2, U1.2 (-)
unnamed: C302.1, R305.1, R306.1, U1.5 (+)
unnamed: R202.1, R205.2, U1.9 (-)
unnamed: R204.2, R206.2, U1.13 (-)
unnamed: C401.2, R405.2, R406.1, R407.1, R408.1, R409.1, U2.2 (-)
unnamed: R812.1, R813.1, U2.5 (+)
unnamed: C802.1, R811.1, R814.2, U2.6 (-)
unnamed: C801.2, R802.1, R803.2, U2.9 (-)
unnamed: R403.1, R404.2, U2.13 (-)
unnamed: C510.2, R517.2, R518.1, U3.2 (-)
unnamed: R511.1, R512.2, U3.5 (+)
unnamed: C502.2, R510.1, R514.2, U3.6 (-)
unnamed: C501.2, R508.1, R509.1, R513.2, U3.9 (-)
unnamed: R503.1, R505.1, U3.12 (+)
unnamed: R620.1, R621.1, U4.3 (+)
unnamed: C602.2, R619.1, R622.2, U4.2 (-)
unnamed: C601.2, R608.1, R609.1, R610.1, R611.2, U4.6 (-)
unnamed: R604.2, R605.1, RV601.2, U4.10 (+)
unnamed: R606.1, R607.2, U4.9 (-)
unnamed: R913.1, R914.1, R915.2, U4.13 (-)
unnamed: C704.2, R710.1, R711.1, R712.2, U5.2 (-)
unnamed: R719.1, R720.1, U5.5 (+)
unnamed: C705.2, R718.1, R721.2, U5.6 (-)
unnamed: R704.1, R705.2, U5.9 (-)
unnamed: C701.1, R702.2, U5.12 (+)
unnamed: R701.1, R703.2, U5.13 (-)
unnamed: R901.1, R902.1, R903.2, U6.2 (-)
unnamed: R927.1, R928.2, U6.6 (-)
unnamed: R907.1, R908.1, R909.2, U6.9 (-)
unnamed: R920.1, R921.1, R922.2, U6.13 (-)

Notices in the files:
hardware/board/mainboard.kicad_pcb:
CERN-OHL-P v2
